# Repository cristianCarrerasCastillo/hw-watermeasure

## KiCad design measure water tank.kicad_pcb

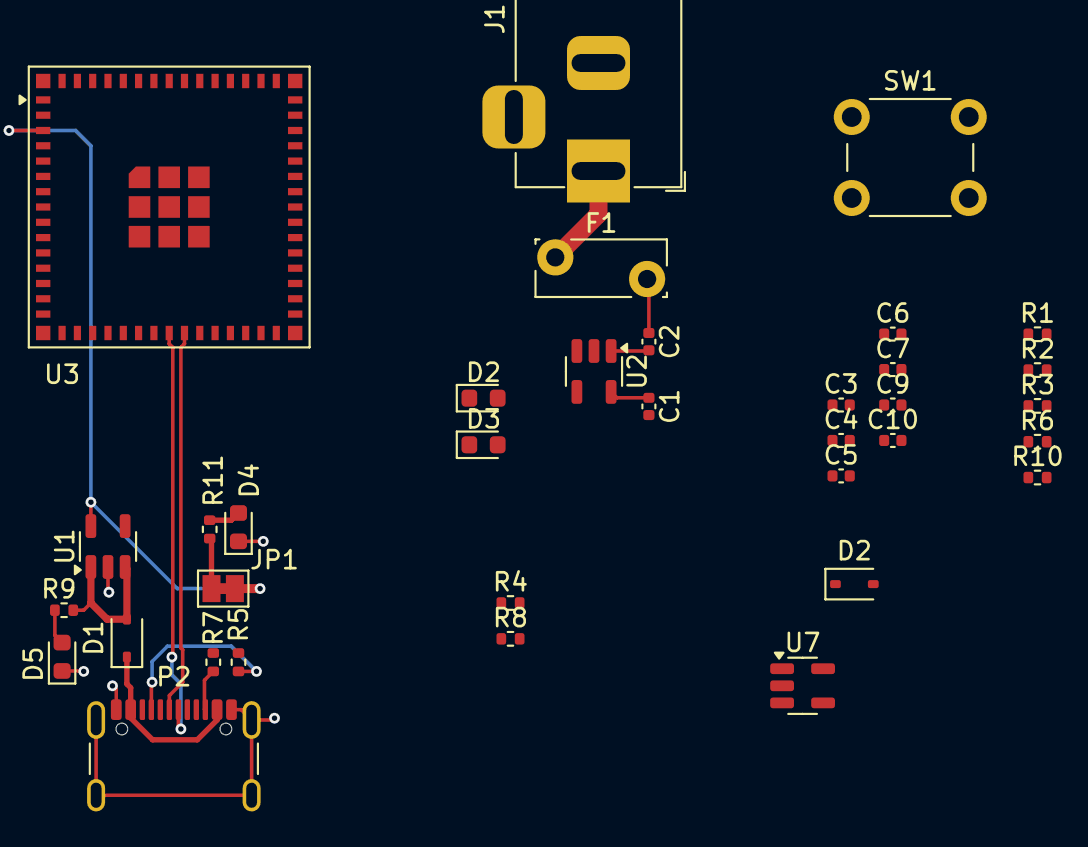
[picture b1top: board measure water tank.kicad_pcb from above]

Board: 2 copper layers, 35 parts (0 on the bottom side), 23 nets.

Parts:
C1, C2, C3: 1uf; C_0402_1005Metric
C4: 10nF/6.3V; C_0402_1005Metric
C5: 470pf; C_0402_1005Metric
C6, C7: 0.1nF/25v; C_0402_1005Metric
C9: 2.2uF; C_0402_1005Metric
C10: 0.1uF; C_0402_1005Metric
D1, D2: BAT60A; D_SOD-323
D2#2: yellow; LED_0603_1608Metric
D3: Red; LED_0603_1608Metric
D4: blue; LED_0603_1608Metric
D5: purple; LED_0603_1608Metric
F1: 600mA; Fuse_Bourns_MF-RG300
J1: Jack-DC; BarrelJack_Horizontal
JP1: SolderJumper-2_P1.3mm_Bridged_Pad1.0x1.5mm
P2: USB_C_Plug_USB2.0; USB_C_Receptacle_GCT_USB4105-xx-A_16P_TopMnt_Horizontal
R1: 50k; R_0402_1005Metric
R2: 30k; R_0402_1005Metric
R3: 10k; R_0402_1005Metric
R4, R8, R9, R11: 4.7k; R_0402_1005Metric
R5, R7: 5.1k; R_0402_1005Metric
R6: 0; R_0402_1005Metric
R10: 100k; R_0402_1005Metric
SW1: SW_Push; SW_PUSH_6mm
U1, U2: SPX3819M5-L; SOT-23-5
U3: ESP32-S3-MINI-1U; ESP32-S2-MINI-1U
U7: RT9080-3.3; SOT-23-5

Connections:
3.3V: C10.1, U7.5 (VOUT)
+3v3: C4.1, C7.1, JP1.2 (B), R3.1, U1.5 (OUT), U3.3 (3V3)
+12V: F1.1, J1.1, R4.1
EN: R3.2, R6.2, R10.2, U3.45 (EN), U7.3 (EN)
GND: C1.2, C3.2, C4.2, C5.2, C6.1, C7.2, C9.2, C10.2, D4.1 (K), D5.1 (K), J1.2, P2.A1 (GND), P2.A12 (GND), P2.B1 (GND), P2.B12 (GND), P2.S1 (SHIELD), R2.2, R5.1, R7.1, SW1.1, U1.2 (GND), U2.2 (GND), U3.1 (GND), U3.2 (GND), U3.42 (GND), U3.43 (GND), U3.46 (GND), U3.47 (GND), U3.48 (GND), U3.49 (GND), U3.50 (GND), U3.51 (GND), U3.52 (GND), U3.53 (GND), U3.54 (GND), U3.55 (GND), U3.56 (GND), U3.57 (GND), U3.58 (GND), U3.59 (GND), U3.60 (GND), U3.61 (GND), U3.62 (GND), U3.63 (GND), U3.64 (GND), U3.65 (GND), U7.2 (GND)
unnamed: C2.1, F1.2
unnamed: C6.2, R6.1, SW1.2
unnamed: D1.1, P2.A4 (VBUS), P2.A9 (VBUS), P2.B4 (VBUS), P2.B9 (VBUS)
unnamed: D2#2.2 (A), R8.1
unnamed: D3.2 (A), R4.2
unnamed: D4.2 (A), R11.2
unnamed: D5.2 (A), R9.2
unnamed: JP1.1 (A), R11.1
unnamed: P2.A5 (CC), R5.2
unnamed: P2.B5 (VCONN), R7.2
unnamed: C5.1, U1.4 (ADJ)
unnamed: R1.2, R2.1, U2.4 (ADJ)
unnamed: C2.2, U2.1 (IN)
unnamed: C1.1, R1.1, R8.2, U2.5 (OUT)
VIN: C9.1, R10.1, U7.1 (VIN)
VUSB: C3.1, D1.2, D2#2.1 (K), D3.1 (K), R9.1, U1.1 (IN), U1.3 (EN)
d+: P2.A6 (D+), U3.24 (IO20)
d-: P2.A7 (D-), U3.23 (IO19)

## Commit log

2024-06-11 fist commit
2024-06-18 add: ch340 changed: esp32
2024-06-19 add: protector de estatica
2024-06-25 del: elimine el ch340 y conecte el usb directamente
